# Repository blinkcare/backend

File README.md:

# Backend

## Setup

Uses: 27 k resistor
An ESP8266

The appropriate libraries.

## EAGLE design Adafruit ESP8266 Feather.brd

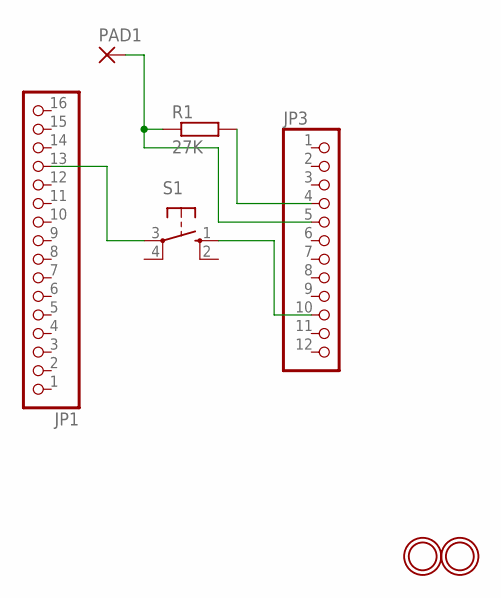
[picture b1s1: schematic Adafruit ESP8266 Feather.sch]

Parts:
JP1: HEADER-1X16ROUND; 1X16_ROUND
JP3: HEADER-1X12; 1X12_ROUND
PAD1: 1,6/0,9
R1: 27K; 0207/10
S1: 10-XX; B3F-10XX
U$31, U$32: MOUNTINGHOLE2.5; MOUNTINGHOLE_2.5_PLATED

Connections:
unnamed: JP3.10, S1.1 (S)
unnamed: JP1.13, S1.3
unnamed: JP3.4, R1.2
unnamed: JP3.5, PAD1.1, R1.1

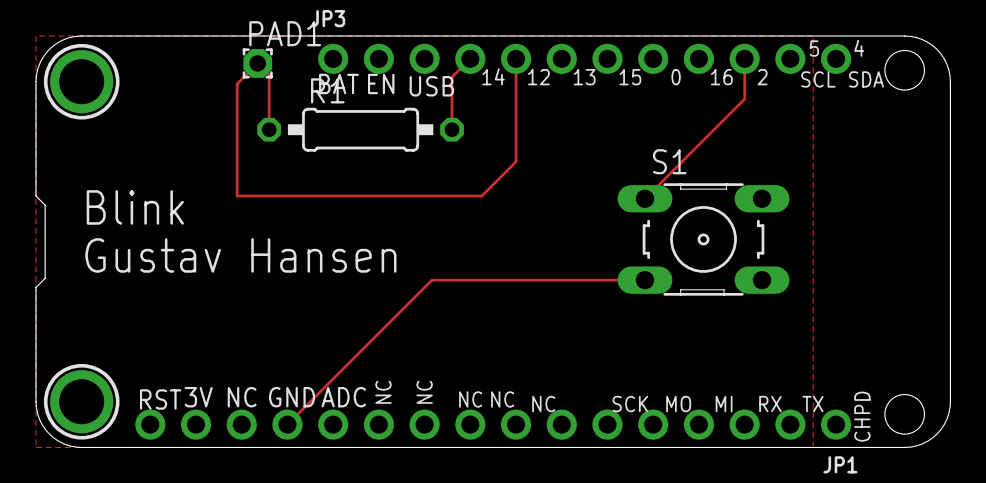
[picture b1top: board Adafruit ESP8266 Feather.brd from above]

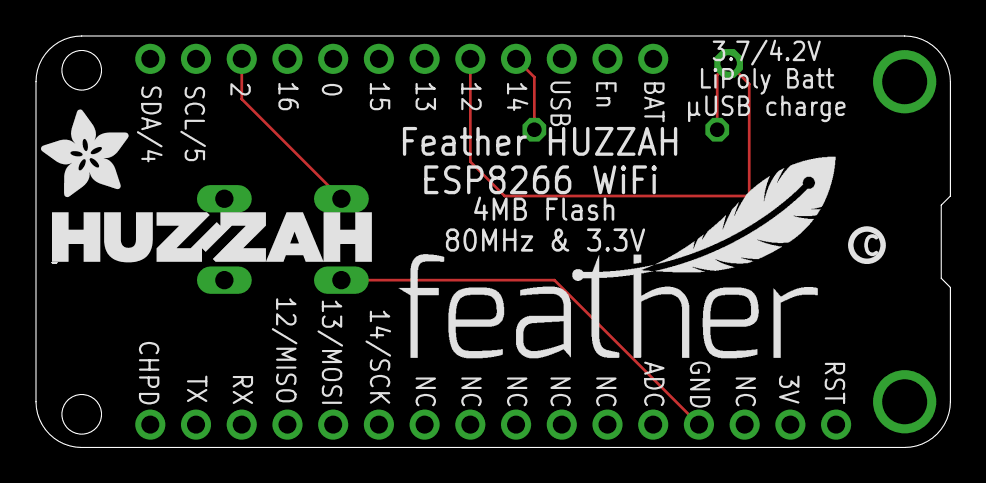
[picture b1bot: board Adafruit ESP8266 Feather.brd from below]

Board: 2 copper layers, 50.8 x 22.9 mm, 11 parts (4 on the bottom side), 4 nets.

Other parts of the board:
U$7: ADAFRUIT_5MM
U$9: FEATHERLOGO
U$13: PCBFEAT-REV-040
U$23: HUZZAHLOGO

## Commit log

2017-09-24 Current non working prototype
2017-09-24 Add tentatively working backend
2017-09-25 Add device name filtering
2017-09-29 Fix small bugs
2017-09-29 Fix constant uploading
2017-09-30 Add button reset
2017-09-30 Fix double slash error
2017-10-01 Add fritzing
2017-10-01 Fix email
2017-11-09 Add carrier board
2017-12-06 Add gerber files, test1
2018-01-25 Update web address

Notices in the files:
parts and their libraries:
microbuilder: This work is placed in the public domain, and may be freely used for commercial and non-commercial work with the following conditions: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
